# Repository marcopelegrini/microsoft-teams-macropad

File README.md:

# Microsoft Teams Macropad

Microsoft Teams Macropad is a physical device, programmed specifically for Microsoft Teams with dedicated keys for triggering functionalities such as "mute" or "raise hand", as well as reactions to meetings and chats!

Documentation: https://pelegrini.ca/hardware/2024/11/10/marcopad/

These are all the asseets I've used to create the macropad. 

Feel free to fork, modify and suggest changes, as long as you keep everything free and never commercialize it.

> This required modifications to Microsoft Teams which are not publicly available yet. So be aware that to take the full advantage of this project you might need to wait until those changes makes into the public available version.<br/><br/>
> Functions that work out-of-the-box are Mute/Unmute and Haise/Lower hands<br/><br/>
> You can also program any of [Microsoft Teams Shortcuts](https://support.microsoft.com/en-us/office/keyboard-shortcuts-for-microsoft-teams-2e8e2a70-e8d8-4a19-949b-4c36dd5292d2) to the other keys instead of the reactions/Copilot ones

Each older in this repo has it's own documentation about each project component

Cheers

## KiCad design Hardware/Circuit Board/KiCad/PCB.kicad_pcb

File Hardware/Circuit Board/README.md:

# Circuit Board

```
Single sided-board milled using a desktop CNC milling machine. The one I've used is discontinued, so I've liked the latest model

PCB design done using KiCad
```

- CNC (similar): [Bantam tools](https://store.bantamtools.com/products/bantam-tools-desktop-cnc-milling-machine)
- Software: [Kicad](https://www.kicad.org/)

KiCad files available in the KiCad folder

I opted for the cheapest setup giving this was going to be my first try.<br/>
I've used an RP2040 USB-C, but a more sophisticated board can be used, for bluetooth connectivity for instance.

The buttons are simple tactile switches I had laying around glued to the "keys" cut from the Façade (front plate).<br/>
You can definitelly do better with proper keyboard switches ([like this guy](https://kbd.news/Mask-keyboard-1819.html)), but I was going with what I had in hand.<br/>

Because I wasn't expecting to use more than one key at the time, I've used a simple matrix keyboard layout **without diodes**, but consider adding diodes in case you're creating combination of keys.<br/>
For instance, you can have multiple layers for even more functions and adding a combination of keys to switch between layers.

For RGB lights, I've used a few neopixels I had laying around. You can do better by using keyboard switches with embedded lights on them.

## Parts
- [Raspberry Pi Pico](https://www.raspberrypi.com/products/raspberry-pi-pico/)
- [Tactile switch](https://www.digikey.ca/en/products/detail/same-sky/TS02-66-60-BK-160-LCR-D/15634268)
- [LED Strip](https://www.adafruit.com/product/1138)

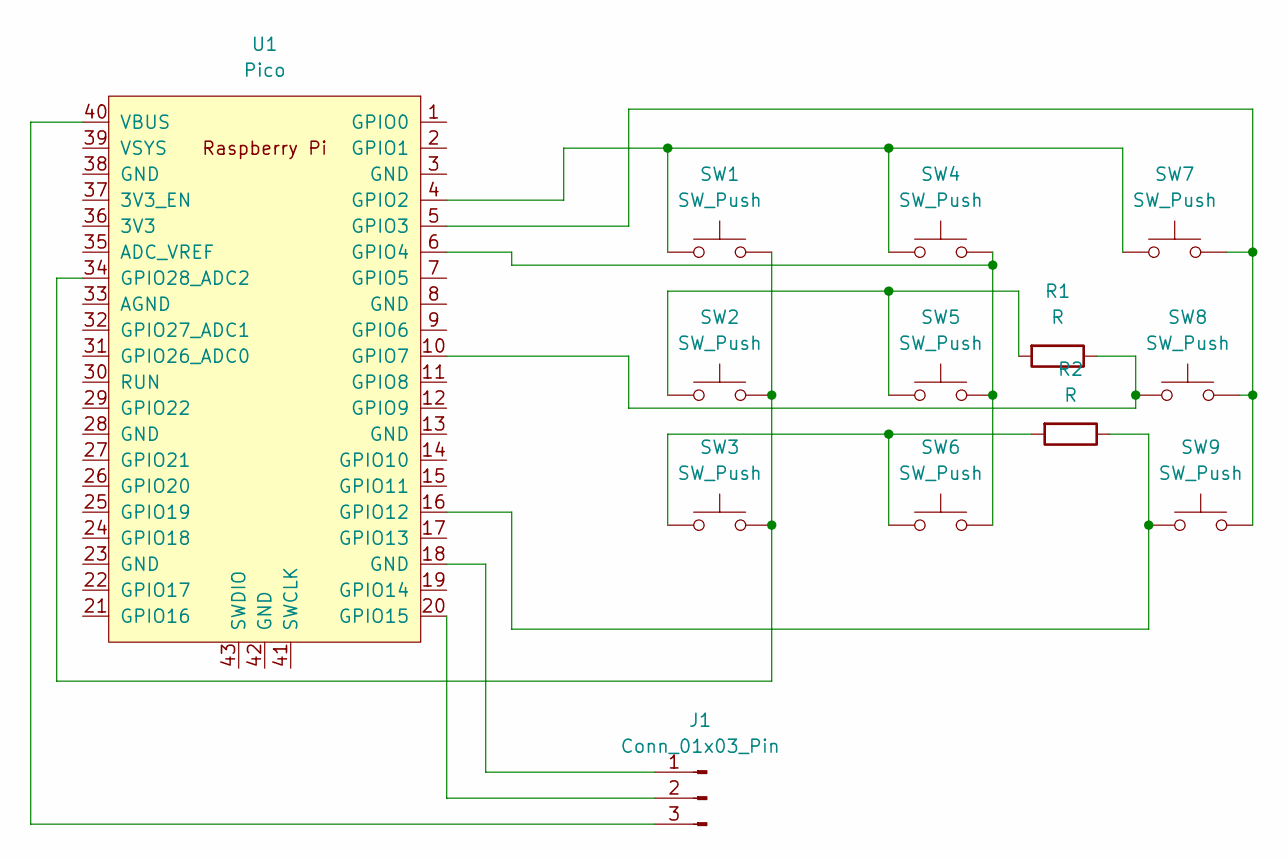
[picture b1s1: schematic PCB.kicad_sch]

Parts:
J1: Conn_01x03_Pin; PinSocket_1x03_P2.54mm_Vertical
R1, R2: R; R_Axial_DIN0207_L6.3mm_D2.5mm_P10.16mm_Horizontal
SW1, SW2, SW3, SW4, SW5, SW6, SW7, SW8, SW9: SW_Push; SW_PUSH_6mm
U1: Pico; RPi_Pico_SMD_TH

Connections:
unnamed: J1.1, U1.18 (GND)
unnamed: J1.2, U1.20 (GPIO15)
unnamed: J1.3, U1.40 (VBUS)
unnamed: R1.2, SW2.1, SW5.1
unnamed: R2.2, SW3.1, SW6.1
unnamed: SW1.1, SW4.1, SW7.1, U1.4 (GPIO2)
unnamed: SW7.2, SW8.2, SW9.2, U1.5 (GPIO3)
unnamed: SW4.2, SW5.2, SW6.2, U1.6 (GPIO4)
unnamed: R1.1, SW8.1, U1.10 (GPIO7)
unnamed: R2.1, SW9.1, U1.16 (GPIO12)
unnamed: SW1.2, SW2.2, SW3.2, U1.34 (GPIO28_ADC2)

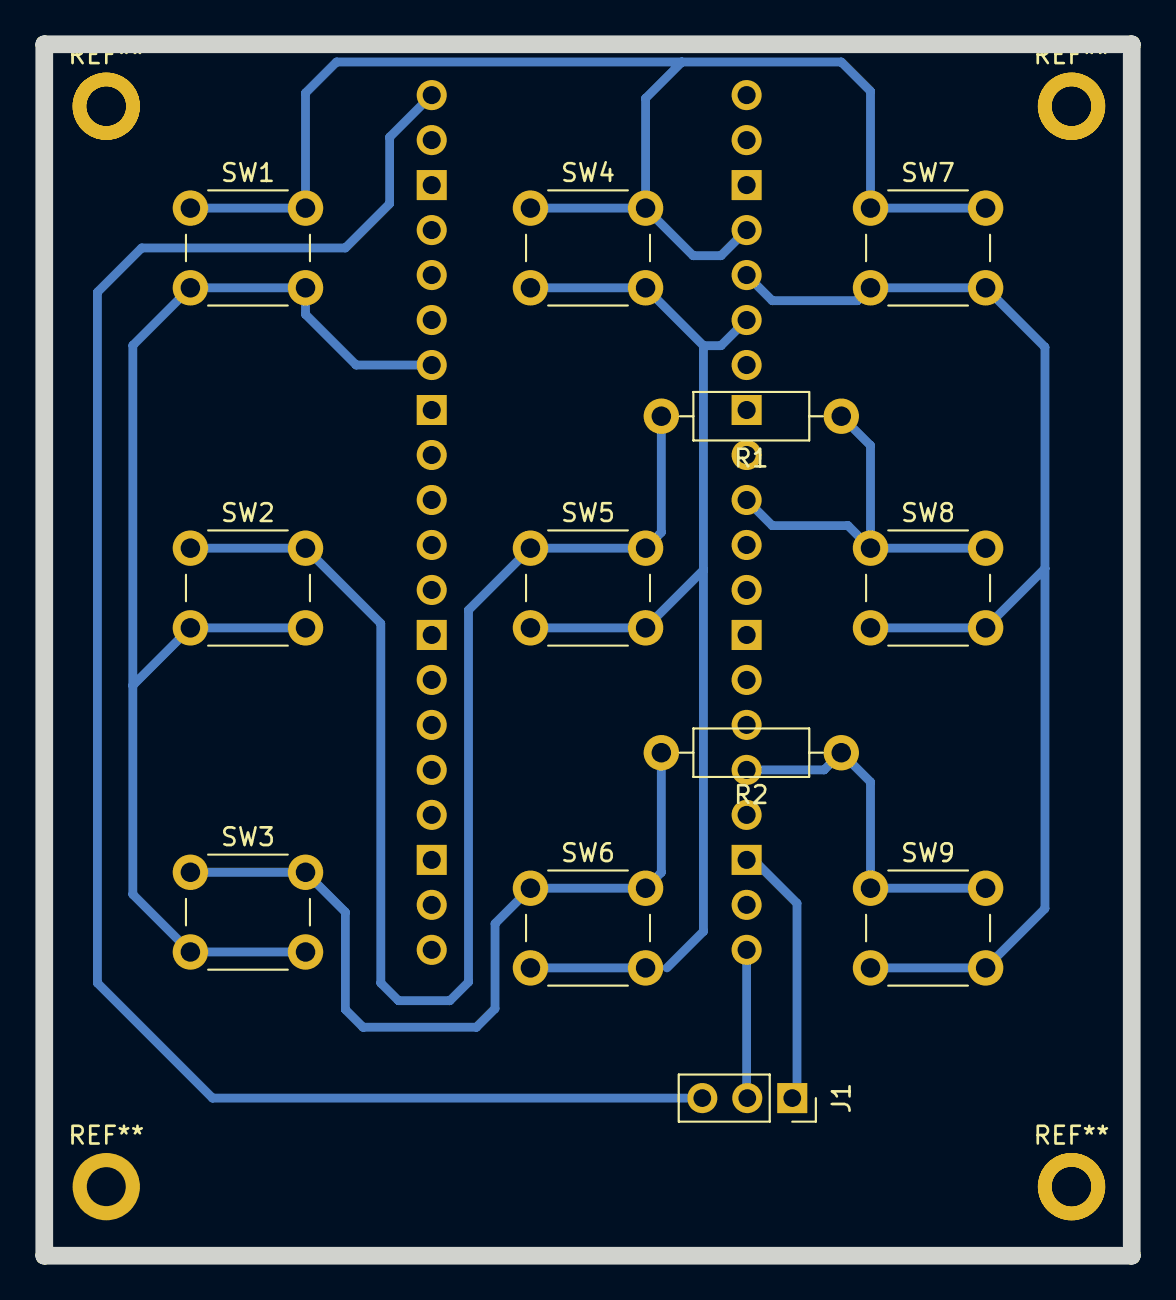
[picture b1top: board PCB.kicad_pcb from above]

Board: 2 copper layers, 61.4 x 68.4 mm, 13 parts (1 on the bottom side), 11 nets.

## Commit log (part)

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2024-09-20 Initial version
